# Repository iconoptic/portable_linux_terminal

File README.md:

# Portable Linux Terminal with Visible Light Communication Keyboard

This project is a **Raspberry Pi-powered cyberdeck** featuring a **detachable keyboard that transmits keystrokes using visible light communication (VLC)**. Built as a senior capstone, it explores embedded systems, optical signaling, and hardware-software co-design.

## Hardware Overview

- **Main Console**: Raspberry Pi 4, 5" DSI touchscreen, lithium battery + charge regulator.
- **Keyboard Module**: 
  - Raspberry Pi Pico
  - 64-key matrix with diode-protected rows/columns
  - RGB LEDs for VLC (Color Shift Keying + PWM)
  - White LED sync pulses for timing
  - Photodiode-based receiver on console side

## Engineering Focus

- Custom **VLC protocol** using PWM + CSK (color shift keying)
- Clock synchronization via **white LED pulses**
- **MOSFET driver design** and RC constant tuning for LED switching
- Ambient light rejection via photodiode spectral filtering
- Safe aluminum plate-based **power delivery system**
- **3D printed case** with access to all ports + GPIO expansion

## Technologies & Tools

- Embedded C++ (Pico SDK)
- GPIO + PWM signal generation
- Eagle/KiCad (PCB design)
- Linux shell scripting + low-level debugging
- Visible light + photodiode interfacing

## Use Case

This build merges protocol design, practical EE, and embedded dev into a portable proof-of-concept for **optical wireless peripherals**. Ideal for R&D, teaching tools in **embedded comms**, **optoelectronics**, or **secure hardware interfaces**.

## License

MIT License

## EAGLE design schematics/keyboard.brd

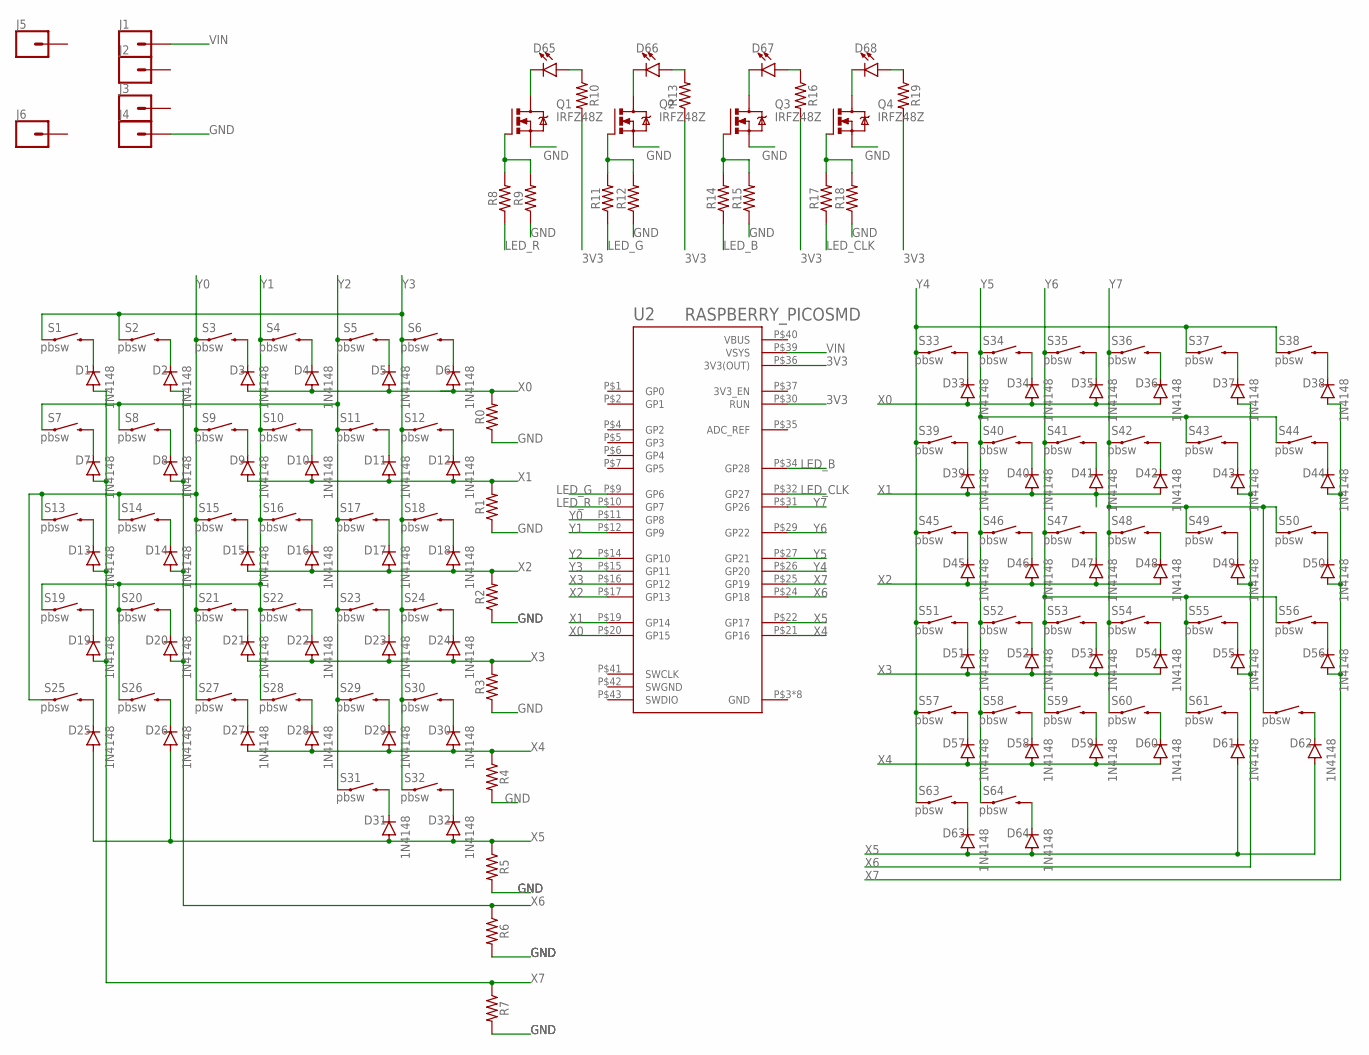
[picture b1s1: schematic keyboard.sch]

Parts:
D1, D2, D3, D4, D5, D6, D7, D8, D9, D10, D11, D12, D13, D14, D15, D16, D17, D18, D19, D20, D21, D22, D23, D24, D25, D26, D27, D28, D29, D30, D31, D32, D33, D34, D35, D36, D37, D38, D39, D40, D41, D42, D43, D44, D45, D46, D47, D48, D49, D50, D51, D52, D53, D54, D55, D56, D57, D58, D59, D60, D61, D62, D63, D64: 1N4148; DO35-7
D65, D66, D67, D68: LED3MM; LED_3MM
J1, J2, J3, J4, J5, J6: CONN_01; 1X01
Q1, Q2, Q3, Q4: IRFZ48Z; TO220BH
R0, R1, R2, R3, R4, R5, R6, R7, R8, R9, R10, R11, R12, R13, R14, R15, R16, R17, R18, R19: AXIAL-0.3
S1, S2, S3, S4, S5, S6, S7, S8, S9, S10, S11, S12, S13, S14, S15, S16, S17, S18, S19, S20, S21, S22, S23, S24, S25, S26, S27, S28, S29, S30, S31, S32, S33, S34, S35, S36, S37, S38, S39, S40, S41, S42, S43, S44, S45, S46, S47, S48, S49, S50, S51, S52, S53, S54, S55, S56, S57, S58, S59, S60, S61, S62, S63, S64: pbsw; TACTILE_SWITCH_PTH_6.0MM
U2: RASPBERRY_PICOSMD; PICO-PKG-SMD

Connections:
3V3: R10.P$2 (2), R13.P$1 (1), R16.P$2 (2), R19.P$2 (2), U2.P$30 (RUN), U2.P$36 (3V3(OUT))
GND: J4.1, Q1.S, Q2.S, Q3.S, Q4.S, R0.P$1 (1), R1.P$1 (1), R2.P$1 (1), R3.P$1 (1), R4.P$2 (2), R5.P$2 (2), R6.P$2 (2), R7.P$2 (2), R9.P$1 (1), R12.P$1 (1), R15.P$1 (1), R18.P$1 (1), U2.P$3 (GND), U2.P$8 (GND), U2.P$13 (GND), U2.P$18 (GND), U2.P$23 (GND), U2.P$28 (GND), U2.P$33 (GND), U2.P$38 (GND)
LED_B: R14.P$1 (1), U2.P$34 (GP28)
LED_CLK: R17.P$1 (1), U2.P$32 (GP27)
LED_G: R11.P$1 (1), U2.P$9 (GP6)
LED_R: R8.P$1 (1), U2.P$10 (GP7)
unnamed: D1.C, S1.3 (2)
unnamed: D2.C, S2.3 (2)
unnamed: D3.C, S3.3 (2)
unnamed: D4.C, S4.3 (2)
unnamed: D5.C, S5.3 (2)
unnamed: D6.C, S6.3 (2)
unnamed: D7.C, S7.3 (2)
unnamed: D8.C, S8.3 (2)
unnamed: D9.C, S9.3 (2)
unnamed: D10.C, S10.3 (2)
unnamed: D11.C, S11.3 (2)
unnamed: D12.C, S12.3 (2)
unnamed: D13.C, S13.3 (2)
unnamed: D14.C, S14.3 (2)
unnamed: D15.C, S15.3 (2)
unnamed: D16.C, S16.3 (2)
unnamed: D17.C, S17.3 (2)
unnamed: D18.C, S18.3 (2)
unnamed: D19.C, S19.3 (2)
unnamed: D20.C, S20.3 (2)
unnamed: D21.C, S21.3 (2)
unnamed: D22.C, S22.3 (2)
unnamed: D23.C, S23.3 (2)
unnamed: D24.C, S24.3 (2)
unnamed: D25.C, S25.3 (2)
unnamed: D26.C, S26.3 (2)
unnamed: D27.C, S27.3 (2)
unnamed: D28.C, S28.3 (2)
unnamed: D29.C, S29.3 (2)
unnamed: D30.C, S30.3 (2)
unnamed: D31.C, S31.3 (2)
unnamed: D32.C, S32.3 (2)
unnamed: D33.C, S33.3 (2)
unnamed: D34.C, S34.3 (2)
unnamed: D35.C, S35.3 (2)
unnamed: D36.C, S36.3 (2)
unnamed: D37.C, S37.3 (2)
unnamed: D38.C, S38.3 (2)
unnamed: D39.C, S39.3 (2)
unnamed: D40.C, S40.3 (2)
unnamed: D41.C, S41.3 (2)
unnamed: D42.C, S42.3 (2)
unnamed: D43.C, S43.3 (2)
unnamed: D44.C, S44.3 (2)
unnamed: D45.C, S45.3 (2)
unnamed: D46.C, S46.3 (2)
unnamed: D47.C, S47.3 (2)
unnamed: D48.C, S48.3 (2)
unnamed: D49.C, S49.3 (2)
unnamed: D50.C, S50.3 (2)
unnamed: D51.C, S51.3 (2)
unnamed: D52.C, S52.3 (2)
unnamed: D53.C, S53.3 (2)
unnamed: D54.C, S54.3 (2)
unnamed: D55.C, S55.3 (2)
unnamed: D56.C, S56.3 (2)
unnamed: D57.C, S57.3 (2)
unnamed: D58.C, S58.3 (2)
unnamed: D59.C, S59.3 (2)
unnamed: D60.C, S60.3 (2)
unnamed: D61.C, S61.3 (2)
unnamed: D62.C, S62.3 (2)
unnamed: D63.C, S63.3 (2)
unnamed: D64.C, S64.3 (2)
unnamed: Q1.G, R8.P$2 (2), R9.P$2 (2)
unnamed: Q4.G, R17.P$2 (2), R18.P$2 (2)
unnamed: D65.K (C), Q1.D
unnamed: D65.A, R10.P$1 (1)
unnamed: D66.K (C), Q2.D
unnamed: Q2.G, R11.P$2 (2), R12.P$2 (2)
unnamed: D66.A, R13.P$2 (2)
unnamed: Q3.G, R14.P$2 (2), R15.P$2 (2)
unnamed: D68.K (C), Q4.D
unnamed: D67.K (C), Q3.D
unnamed: D67.A, R16.P$1 (1)
unnamed: D68.A, R19.P$1 (1)
SWGND: U2.P$42 (SWGND)
VBUS: U2.P$40 (VBUS)
VIN: J1.1, U2.P$39 (VSYS)
X0: D3.A, D4.A, D5.A, D6.A, D33.A, D34.A, D35.A, D36.A, R0.P$2 (2), U2.P$20 (GP15)
X1: D9.A, D10.A, D11.A, D12.A, D39.A, D40.A, D41.A, D42.A, R1.P$2 (2), U2.P$19 (GP14)
X2: D15.A, D16.A, D17.A, D18.A, D45.A, D46.A, D47.A, D48.A, R2.P$2 (2), U2.P$17 (GP13)
X3: D21.A, D22.A, D23.A, D24.A, D51.A, D52.A, D53.A, D54.A, R3.P$2 (2), U2.P$16 (GP12)
X4: D27.A, D28.A, D29.A, D30.A, D57.A, D58.A, D59.A, D60.A, R4.P$1 (1), U2.P$21 (GP16)
X5: D25.A, D26.A, D31.A, D32.A, D61.A, D62.A, D63.A, D64.A, R5.P$1 (1), U2.P$22 (GP17)
X6: D2.A, D8.A, D14.A, D20.A, D37.A, D43.A, D49.A, D55.A, R6.P$1 (1), U2.P$24 (GP18)
X7: D1.A, D7.A, D13.A, D19.A, D38.A, D44.A, D50.A, D56.A, R7.P$1 (1), U2.P$25 (GP19)
Y0: S3.1, S9.1, S13.1, S14.1, S15.1, S21.1, S25.1, S27.1, U2.P$11 (GP8)
Y1: S4.1, S10.1, S16.1, S19.1, S20.1, S22.1, S26.1, S28.1, U2.P$12 (GP9)
Y2: S5.1, S7.1, S8.1, S11.1, S17.1, S23.1, S29.1, S31.1, U2.P$14 (GP10)
Y3: S1.1, S2.1, S6.1, S12.1, S18.1, S24.1, S30.1, S32.1, U2.P$15 (GP11)
Y4: S33.1, S37.1, S38.1, S39.1, S45.1, S51.1, S57.1, S63.1, U2.P$26 (GP20)
Y5: S34.1, S40.1, S43.1, S44.1, S46.1, S52.1, S58.1, S64.1, U2.P$27 (GP21)
Y6: S35.1, S41.1, S47.1, S53.1, S55.1, S56.1, S59.1, S61.1, U2.P$29 (GP22)
Y7: S36.1, S42.1, S48.1, S49.1, S50.1, S54.1, S60.1, S62.1, U2.P$31 (GP26)

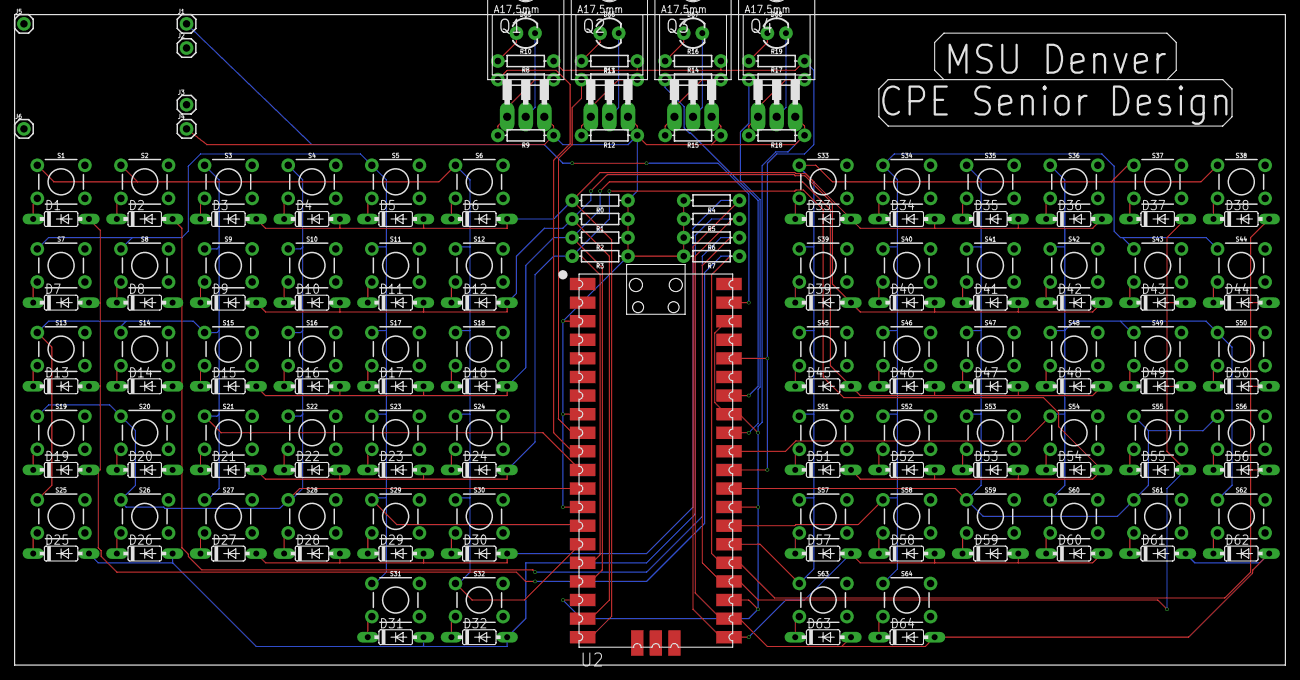
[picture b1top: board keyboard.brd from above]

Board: 2 copper layers, 173.7 x 88.9 mm, 163 parts (0 on the bottom side), 99 nets.

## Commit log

2023-01-30 fixed gitignore
2023-01-30 Fixed memory overflow
2023-02-04 added initial led PWM output
2023-02-09 added sdk import file to gitignore
2023-02-10 Added README.md with build instructions.
2023-02-11 switched to pull-up configuration
2023-02-13 PWM code added to function
2023-02-13 Revert to "07ef8e4"
2023-02-17 Updated PWM code
2023-02-20 Progress on writing custom LED message
2023-02-22 Manual interrupt handling
2023-02-23 fixed lockup
2023-03-10 fixed top two rows
2023-04-11 Updated pin assignments for PCB
2023-04-11 Schematics finalized for PCB 1.0
2023-04-11 Initial code for n-key rollover
2023-04-12 Fixed n-key tx
2024-08-20 Final Design Document
2024-08-20 Prototype Photo
2024-08-20 Rename IMG20230505115222(2).jpg to prototype.jpg

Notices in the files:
parts and their libraries:
SparkFun-Resistors: Licensing: Creative Commons ShareAlike 4.0 International - https://creativecommons.org/licenses/by-sa/4.0
